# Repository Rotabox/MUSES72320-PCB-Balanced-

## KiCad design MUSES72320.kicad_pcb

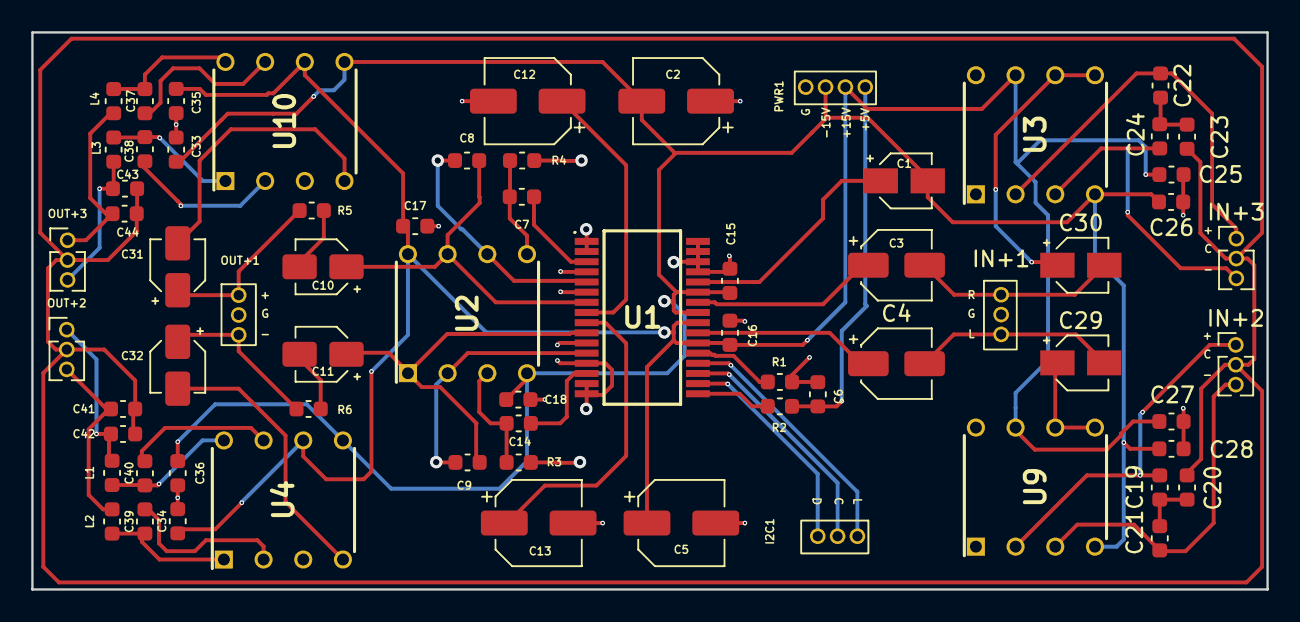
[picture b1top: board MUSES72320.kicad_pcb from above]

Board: 2 copper layers, 79.1 x 35.7 mm, 68 parts (0 on the bottom side), 51 nets.

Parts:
C1: 10uF; CP_Elec_3x5.3
C2, C5, C12, C13: 100uF; CP_Elec_5x5.3
C3, C4: 22uF; CP_Elec_4x5.3
C6: 1uF; C_0603_1608Metric
C7, C14, C37, C38, C39, C40: 10uF; C_0603_1608Metric
C8, C9: 10pF; C_0603_1608Metric
C10, C11, C31, C32: 10uF; CP_Elec_3x5.4
C15, C16, C17, C18, C25, C26, C27, C28, C33, C34, C35, C36: 0.1uF; C_0603_1608Metric
C19, C21, C22, C24: 470pF; C_0603_1608Metric
C20, C23: 47pF; C_0603_1608Metric
C29, C30: 100uF; CP_Elec_3x5.3
C41, C42, C43, C44: 100pF; C_0603_1608Metric
I2C1: Conn_01x04_Male; PinHeader_1x04_P1.27mm_Vertical
IN+1: Conn_01x04_Male; PinHeader_1x04_P1.27mm_Vertical
IN+2, IN+3: Conn_01x04_Male; PinHeader_1x03_P1.27mm_Vertical
L1, L2, L3, L4: L_Ferrite; C_0603_1608Metric
OUT+1: Conn_01x04_Male; PinHeader_1x04_P1.27mm_Vertical
OUT+2, OUT+3: Conn_01x04_Male; PinHeader_1x03_P1.27mm_Vertical
PWR1: PWR; PinHeader_1x04_P1.27mm_Vertical
R1, R2: 10K; C_0603_1608Metric
R3, R4: 470K; C_0603_1608Metric
R5, R6: 47R; C_0603_1608Metric
U1: MUSES72320V-TE2; SOP65P760X145-32N
U2: MUSES02; DIP762W56P254L880H425Q8N
U3, U9: 1240P08-U; DIP762W56P254L880H425Q8N
U4, U10: that1646; DIP762W56P254L880H425Q8N

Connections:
+5V: C6.2, PWR1.4, R2.2
+15V: C5.1, C16.2, C17.2, C25.1, C27.1, C34.1, C35.1, PWR1.3, U1.22 (V+_1), U1.24 (V+_2), U2.8 (V+), U3.7 (VCC), U4.6 (V+), U9.7 (VCC), U10.6 (V+)
-15V: C1.2, C2.2, C15.2, C18.1, C26.1, C28.1, C33.1, C36.1, PWR1.2, U1.25 (V-_1), U1.27 (V-_2), U2.4 (V-), U3.4 (VEE), U4.5 (V-), U9.4 (VEE), U10.5 (V-)
Earth: C20.1, C23.1, C41.1, C42.1, C43.1, C44.1, IN+2.2, IN+3.2, OUT+2.2, OUT+3.2
GNDPWR: C2.1, C5.2, C6.1, C12.2, C13.2, C15.1, C16.1, C17.1, C18.2, C25.2, C26.2, C27.2, C28.2, C33.2, C34.2, C35.2, C36.2, IN+1.2, R1.2, R3.2, R4.1, U1.1 (Z/C_REFL), U1.2 (L_REF_1), U1.4 (L_REF_2), U1.6 (L_REF_3), U1.11 (R_REF_1), U1.13 (R_REF_2), U1.15 (R_REF_3), U1.16 (Z/C_REFR), U1.29 (ADR2), U1.30 (ADR1), U1.31 (ADR0), U1.32 (Z/C), U3.1 (REF), U4.3, U9.1 (REF), U10.3
unnamed: C1.1, U1.28 (D_CAP)
unnamed: C3.1, U1.26 (INL)
unnamed: C3.2, C30.2, IN+1.1
unnamed: C4.1, U1.23 (INR)
unnamed: C4.2, C29.2, IN+1.3
unnamed: C7.1, U1.3 (L+)
unnamed: C7.2, R4.2, U2.5 (B_+INPUT)
unnamed: C8.1, U1.5 (L-), U2.6 (B_-INPUT)
unnamed: C9.1, U1.12 (R-), U2.2 (A_-INPUT)
unnamed: C8.2, C10.1, U1.7 (OUTL), U2.7 (B_OUTPUT)
unnamed: C10.2, R5.2
unnamed: C9.2, C11.1, U1.10 (OUTR), U2.1 (A_OUTPUT)
unnamed: C11.2, R6.2
unnamed: C12.1, U1.8 (DCCAP_L)
unnamed: C13.1, U1.9 (DCCAP_R)
unnamed: C14.1, U1.14 (R+)
unnamed: C14.2, R3.1, U2.3 (A_+INPUT)
unnamed: C19.1, IN+2.1, U9.2 (IN+)
unnamed: C19.2, C20.2, C21.1
unnamed: C21.2, IN+2.3, U9.3 (IN-)
unnamed: C22.1, IN+3.1, U3.2 (IN+)
unnamed: C22.2, C23.2, C24.1
unnamed: C24.2, IN+3.3, U3.3 (IN-)
unnamed: C29.1, U9.5 (SENSE), U9.6 (VOUT)
unnamed: C30.1, U3.5 (SENSE), U3.6 (VOUT)
unnamed: C31.1, OUT+1.1, R5.1
unnamed: C32.1, OUT+1.3, R6.1
unnamed: C38.1, L3.1, U10.1
unnamed: C40.1, L1.1, U4.8
unnamed: C44.2, L4.2, OUT+3.1
unnamed: I2C1.2, U1.19 (CLOCK)
unnamed: I2C1.3, U1.18 (DATA)
unnamed: I2C1.1, U1.20 (LATCH)
unnamed: C42.2, L1.2, OUT+2.1
unnamed: C41.2, L2.2, OUT+2.3
unnamed: C43.2, L3.2, OUT+3.3
unnamed: R1.1, U1.21 (D_REF)
unnamed: R2.1, U1.17 (D_VDD)
unnamed: C39.1, L2.1, U4.1
unnamed: C39.2, U4.2 (2A)
unnamed: C32.2, U4.4
unnamed: C40.2, U4.7 (1A)
unnamed: C38.2, U10.2 (2A)
unnamed: C31.2, U10.4
unnamed: C37.2, U10.7 (1A)
unnamed: C37.1, L4.1, U10.8
